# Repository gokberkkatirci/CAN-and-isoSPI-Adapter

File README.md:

# CAN and isoSPI Adapters

Two USB adapters for battery-management bench work. Both connect a host PC to isolated Classical CAN and isoSPI, with socketed controller modules and switchable CAN termination.

| | [Nano R4 · R0E](#nano-r4-adapter-r0e) | [Teensy 4.1 · T41-R0C](#teensy-41-adapter-t41-r0c) |
|---|:---:|:---:|
| Top view |  |  |
| Controller | Arduino Nano R4 (socketed) | Teensy 4.1 (socketed) |
| USB | Nano's own USB-C | Carrier USB-C for power and data |
| CAN ports | 1, screw terminal | 6, vertical DSUB-9 female (CiA 303-1 pinout) |
| CAN isolation | ISO1042 with isolated 5 V supply | Six independent ISO1042 channels, each with its own isolated 5 V supply |
| CAN termination | 120 Ω slide switch | 120 Ω slide switch on every port |
| isoSPI ports | 2 (MAIN, AUX) | 6 |
| Board | 82 × 64 mm, 4 layers | 216 × 120 mm, 6 layers |
| Prototype files | [Nano Gerbers, BOM and CPL](manufacturing/prototype/R0E/) | [Teensy Gerbers, BOM and CPL](manufacturing/prototype/T41-R0C/) |

> **Prototype status.** Both boards pass their recorded KiCad ERC, DRC and schematic-parity checks. Every JLCPCB part on both BOMs was in stock on 2026-11-24. Hardware bring-up and insulation qualification are pending. The 1,000 V DC pack and 3 m isoSPI cable targets remain unqualified. The manufacturing files are for prototype review. See the [bench verification plan](tests/verification-plan.md).

## Nano R4 adapter (R0E)

| Interface | Hardware |
|---|---|
| Controller | Arduino Nano R4 with headers (ABX00143), installed in J1/J2 |
| CAN | ISO1042DWR, up to 1 Mbit/s, isolated regulated supply, TVS and switchable 120 Ω |
| isoSPI | ADBMS6822 with MAIN and AUX on separate floating twisted pairs |
| isoSPI magnetics | Two CND-tek HM1238NLTP transformers, each specified for 1,000 V DC working voltage and basic insulation |

Orient the board with USB-C at the top. The left terminal is marked **CAN H**, **CAN L** and **GND** from top to bottom. This GND is the isolated CAN reference. Set the slide switch to **120R** when the adapter terminates an end of the bus. The two right terminals are **MAIN** and **AUX**, each a floating differential pair with **+** above **−**.

| Nano pins | Function |
|---|---|
| D4 / D5 | CAN TX / RX |
| D8 / A3 | CAN supply enable, active high / fault, active low |
| D13 / D11 / D12 | SPI clock / controller out / controller in |
| D10 / D9 | MAIN / AUX chip select |
| D2 / D3 | MAIN / AUX interrupt status |
| D6 / D7 | MAIN / AUX wake status |

R0E replaces three parts that JLCPCB no longer stocked: the isoSPI transformers (now HM1238NLTP), the CAN supply transformer (now MXPP6-3K6110) and the CAN LDO (now TPS7A1650-Q1). See the [R0E notes](docs/r0e.md). Mounting hole H3 is close to the AUX terminal and must take **nylon hardware only**; the silkscreen says so ([R0D notes](docs/r0d.md)).

- [KiCad project](hardware/kicad/CAN_isoSPI_adapter.kicad_pro), [schematic](hardware/kicad/CAN_isoSPI_adapter.kicad_sch) and [routed PCB](hardware/kicad/CAN_isoSPI_adapter.kicad_pcb)
- [Nano R4 firmware](firmware/README.md#nano-r4-adapter)
- [R0E fabrication files](manufacturing/prototype/R0E/README.md) and [checks](tests/R0E/)

## Teensy 4.1 adapter (T41-R0C)

Six isolated CAN ports on DSUB-9 connectors along one long edge and six isoSPI terminals along the opposite long edge. **Channel N** is one column: CAN N sits directly opposite isoSPI N, numbered 1–6 from left to right, and the same number is used on the silkscreen, in the schematic, in reference designators and in the firmware. Each adapter reports a unique ID and an optional stored label, so several can share one host. A single USB-C connector supplies power and USB data; the data lines reach the Teensy through two pogo pins that touch its USB device pads. **Keep the Teensy's VIN–VUSB pads joined** and never plug its own micro-USB.

> **Before powered bring-up:** Resolve the six direct ADBMS6822 INTR connections to the Teensy’s 3.3 V inputs.

R0C replaces the same three out-of-stock parts as the Nano R0E ([T41-R0C notes](docs/t41-r0c.md)). R0B fixed the USB path of R0A: the Teensy VUSB pin is powered again, the D+/D− lines lost their 90 mm test-pad stubs, and VBUS runs on a 1 mm outer-layer track ([T41-R0B notes](docs/t41-r0b.md)).

| Interface | Hardware |
|---|---|
| Controller | Teensy 4.1 with pins, in two 1 × 24 sockets |
| CAN1–CAN3 | Teensy FlexCAN1–3 (CAN3 is CAN FD capable) |
| CAN4–CAN6 | MCP2518FD controllers on SPI1, 40 MHz crystals |
| Each CAN port | ISO1042DWR, TPS2553 current-limited switch, SN6505B + MXPP6-3K6110 isolated supply, TPS7A1650-Q1 LDO, PESD2CANFD24V TVS, 120 Ω switch, power LED |
| CAN connector | DSUB-9 female: pin 2 CAN_L, pin 7 CAN_H, pins 3 and 6 CAN_GND, pin 5 and shell to a 1 MΩ ∥ 4.7 nF shield network |
| isoSPI | Three ADBMS6822, six HM1238NLTP transformers, six two-pole terminals |
| USB-C | 5.1 kΩ CC pull-downs read by the Teensy for power budgeting, USBLC6 ESD, 2 A PTC, SMAJ5.0A |

- [User manual](docs/user-manual-t41.md) — assembly, flashing, commands and usage examples
- [Hardware notes and pin map](hardware/teensy41/README.md)
- [KiCad project](hardware/teensy41/CAN6_isoSPI6_T41.kicad_pro), generated from [design.py](hardware/teensy41/tools/design.py)
- [Teensy firmware](firmware/README.md#teensy-41-adapter)
- [R0C fabrication files for JLCPCB](manufacturing/prototype/T41-R0C/README.md) and [checks](tests/T41-R0C/)

## Shared documentation

- [Design rationale](docs/hardware-plan.md), [decisions](docs/decisions.md), [component sourcing](docs/components.md) and [references](docs/references.md)
- [Bench verification plan](tests/verification-plan.md)
- [3D model sources](hardware/kicad/models/README.md) and [third-party materials](THIRD_PARTY.md)

## Prototype limits

The PCB rules require **8 mm copper clearance** around each floating isoSPI cable domain. The **1 kV DC** transformer working rating applies to the HM1238NLTP, which provides basic insulation. Protective insulation still needs to be established for the complete system, including PCB creepage, mounting, cables and enclosure. The CAN ports are intended for low-voltage CAN networks.

On 2026-11-24 JLCPCB stocked every part. The scarcest parts limit an order to about 23 Teensy boards or 139 Nano boards ([stock list](docs/components.md#stock-check-2026-11-24)). Recheck stock, placement rotations, through-hole assembly and socket fit before ordering. See the [design decisions](docs/decisions.md) and [manufacturing workflow](manufacturing/README.md).

No license has been selected yet; see [publication notes](docs/publication.md).

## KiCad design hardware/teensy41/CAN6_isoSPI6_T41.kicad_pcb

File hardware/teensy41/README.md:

# Teensy 4.1 adapter — six CAN, six isoSPI (R0C)

Open [CAN6_isoSPI6_T41.kicad_pro](CAN6_isoSPI6_T41.kicad_pro) in **KiCad 10.0.6**. The schematic, PCB placement, zones, design rules and manufacturing CSVs are generated from [tools/design.py](tools/design.py) by [tools/generate_t41.py](tools/generate_t41.py). Edit `design.py` and regenerate rather than editing the schematic and board separately. The R0B USB rework was applied to the routed R0A board with [tools/rework_r0b.py](tools/rework_r0b.py) ([T41-R0B notes](../../docs/t41-r0b.md)). The R0C part swap for JLCPCB stock was applied to the R0B board with [tools/rework_r0c.py](tools/rework_r0c.py) ([T41-R0C notes](../../docs/t41-r0c.md)).

## Board

- **216 × 120 mm**, six layers, 1.6 mm, six M3 holes, all passives 1206.
- **Bottom edge:** six vertical DSUB-9 female connectors (mating face up, 4-40 standoffs), CAN1 on the left. Each has its own 120 Ω slide switch (**120R** / **OFF**) and a green LED that lights when its isolated supply is on.
- **Top edge:** six isoSPI terminals, each directly opposite the CAN port with the same number; **+** is on the left of each pair.
- **Left edge:** USB-C for power and data. The Teensy plugs into J2/J3 with its USB end toward the USB-C connector.

| Layer | Use |
|---|---|
| F.Cu | Components, signals and ground fanouts |
| In1.Cu | Logic ground plane; a separate ground plane for each isolated CAN port |
| In2.Cu | Signals |
| In3.Cu | Signals and a +5 V pour |
| In4.Cu | Second logic ground plane and per-port isolated ground planes |
| B.Cu | Signals, logic ground pour and per-port isolated ground pours |

The isoSPI cable side of each transformer has no plane under it and keeps 8 mm of copper clearance to everything else. Each CAN port's isolated domain is kept 3 mm away from logic copper and from its neighbours. Both rules are in [CAN6_isoSPI6_T41.kicad_dru](CAN6_isoSPI6_T41.kicad_dru).

## Channel addressing

Channel **N** is one column of the board: DSUB-9 **CAN N** on the bottom edge and terminal **isoSPI N** directly above it on the top edge. Channels are numbered 1–6 from left to right, viewed from the component side with USB-C on the left. The same number is used on the silkscreen, in the schematic net names (`CANn_*`, `ISOn_*`), the reference designators (CAN parts are numbered n01–n12, so channel 4 uses U401, J401, SW401…) and the firmware commands.

| Channel | CAN controller | isoSPI bridge | Bridge channel |
|---|---|---|---|
| 1 | FlexCAN1 | U701 | 2 |
| 2 | FlexCAN2 | U701 | 1 |
| 3 | FlexCAN3 (CAN FD capable) | U801 | 2 |
| 4 | MCP2518FD U405 | U801 | 1 |
| 5 | MCP2518FD U505 | U901 | 2 |
| 6 | MCP2518FD U605 | U901 | 1 |

isoSPI transformers and terminals use T7xx/J7xx for channels 1–2, T8xx/J8xx for 3–4 and T9xx/J9xx for 5–6. Each adapter reports a factory-unique ID over USB, and a user label can be stored in EEPROM, so several adapters on one host can be addressed reliably. See the [firmware commands](../../firmware/README.md#usb-serial-commands-1).

## Test points

Thirteen 1.5 mm test pads are placed in two groups between the Teensy and the right mounting hole. Probe them with an oscilloscope or multimeter during bring-up.

| Label | Net | Group | Row |
|---|---|---|---|
| 5V | +5V | Left | 1 |
| GND | GND | Left | 1 |
| 3V3 | +3.3V | Left | 1 |
| FLT | CAN_PWR_FAULT | Left | 2 |
| D32 | Teensy pin 32 (spare) | Left | 2 |
| MOSI | ISO_MOSI (isoSPI SPI) | Right | 1 |
| MISO | ISO_MISO | Right | 1 |
| SCK | ISO_SCK | Right | 1 |
| TX1 | CAN1_TX (FlexCAN1) | Right | 1 |
| RX1 | CAN1_RX | Right | 1 |
| MOSI1 | MCP_MOSI (SPI1) | Right | 2 |
| MISO1 | MCP_MISO | Right | 2 |
| SCK1 | MCP_SCK | Right | 2 |

R0A also had VBUS, D+ and D− pads (TP4, TP7, TP8). R0B removed them because their long routes split the +5 V pour and put 90 mm stubs on the USB pair. The other pads keep their numbers.

## 3D view

Every fitted part has a model. Standard parts use the KiCad 10 library; the ADBMS6822, transformers, slide switch, pogo pins, USB-C receptacle and a mounted Teensy 4.1 use drawing-based VRML models from [../kicad/models](../kicad/models/README.md). Open **View → 3D Viewer** or run `kicad-cli pcb render --quality high`.

## Before first power-up

1. **Keep the VIN–VUSB pads joined** on the Teensy's underside (the factory state). The carrier feeds VIN from +5 V through D2 (Schottky), after F1 (2 A PTC), and the joined pads pass that supply on to VUSB, which powers the Teensy's USB PHY. R0A said to cut the pads; with them cut the Teensy will not enumerate.
2. Use the carrier USB-C only. J4 and J5 are pogo pins that press on the Teensy's USB device D−/D+ pads, so the Teensy enumerates and is programmed through the carrier connector. **Never plug the Teensy's micro-USB** while it is on the carrier: the carrier would drive 5 V back into that host port through VUSB.
3. Measure the D−/D+ pad positions on your Teensy against J4/J5 before assembly; see [open items](../../docs/decisions.md#teensy-41-adapter-decisions-r0a-2026-11-08). Check that the pogo pins stand upright after reflow, or fit them by hand as described in the [manufacturing notes](../../manufacturing/prototype/T41-R0C/README.md).

## CAN port wiring

| DSUB-9 pin | Signal |
|---|---|
| 2 | CAN_L |
| 7 | CAN_H |
| 3, 6 | Isolated CAN ground of that port |
| 5, shell | Shield, to that port's ground through 1 MΩ ∥ 4.7 nF 2 kV |
| 1, 4, 8, 9 | Not connected |

This is the CiA 303-1 layout used by PEAK PCAN adapters, so standard CAN cables and termination plugs fit.

## Teensy 4.1 pin map

| Teensy pin | Function | Teensy pin | Function |
|---|---|---|---|
| 22 / 23 | CAN1 TX / RX (FlexCAN1) | 17, 18, 19, 20, 21, 24 | CAN1–CAN6 supply enable, active high |
| 1 / 0 | CAN2 TX / RX (FlexCAN2) | 25 | CAN supply fault, wired-OR, active low |
| 31 / 30 | CAN3 TX / RX (FlexCAN3, FD capable) | 26 / 39 / 27 | SPI1 MOSI / MISO / SCK to MCP2518FD |
| 11 / 12 / 13 | SPI MOSI / MISO / SCK to ADBMS6822 | 38, 37, 36 | CAN4, CAN5, CAN6 MCP2518FD chip select |
| 10, 9, 8, 7, 6, 5 | isoSPI port 1–6 chip select | 35, 34, 33 | CAN4, CAN5, CAN6 MCP2518FD interrupt |
| 2, 3, 4, 14, 15, 16 | isoSPI port 1–6 INTR | 40 / 41 | USB-C CC1 / CC2 sense through 1 kΩ |
| 28 / 29 | Green OK LED / red fault LED | 32 | Spare, test pad TP6 (D32) |

Logic runs at 3.3 V from the Teensy's regulator. ADBMS6822 VDDS and MSTR use 3.3 V; VDD and VP use 5 V. ISO1042 VCC1 is 3.3 V and VCC2 is the port's isolated 5 V.

## Power

USB-C VBUS → 1 mm B.Cu track → F1 → SMAJ5.0A → +5 V plane; D2 feeds the Teensy VIN from +5 V. Each CAN port has a TPS2553 switch limited to about 200 mA (R_ILIM = 130 kΩ) feeding an SN6505B push-pull driver, a Maxinmicro MXPP6-3K6110 1:1.1 transformer, two B5819W rectifiers and a TPS7A1650-Q1 5 V LDO (100 mA; near dropout at full load, see [T41-R0C notes](../../docs/t41-r0c.md#still-open)). The switches stay off until firmware opens a port. Provisional worst case is about 110 mA from 5 V per transmitting CAN port plus about 250 mA for the Teensy, bridges and controllers, so all six ports need a 1.5 A or 3 A USB-C source. The firmware reads the source's CC advertisement and limits a default USB port to two open CAN ports.

## Regenerating

```sh
PY=/Applications/KiCad/KiCad.app/Contents/Frameworks/Python.framework/Versions/Current/bin/python3
export JAVA=/path/to/java FREEROUTING_JAR=/path/to/freerouting.jar
$PY hardware/teensy41/tools/generate_t41.py pcb      # schematic, project, rules, placement, ground and QFN fan-out
$PY hardware/teensy41/tools/generate_t41.py route    # Freerouting 2.x through a Specctra round trip
$PY hardware/teensy41/tools/generate_t41.py patch    # pours, zone fill, close leftovers, trim dangling copper
$PY hardware/teensy41/tools/generate_t41.py fab manufacturing/prototype/T41-R0C
```

How the generator gets a clean route:

- Every ground pad is fanned out to its plane before routing, and each ADBMS6822 pin gets a fixed escape to a via ring around the QFN, because an autorouter cannot reliably escape a 0.5 mm-pitch QFN with neighbouring decoupling.
- For routing, each ground pad and its fan-out get a private net, and the two ground-plane layers are removed from the Specctra file. The router therefore only uses F.Cu, In2, In3 and B.Cu, and leaves the planes intact.
- The isoSPI band and the CAN isolation gaps are temporary keepouts during routing; the final board checks them with the DRC rules instead.

Routing is not deterministic, so a regenerated board needs a new DRC run and a new manufacturing package. The `pcb` stage overwrites the routed board. The committed board reports zero ERC, DRC, unconnected-item and schematic-parity findings at all severities in KiCad 10.0.8 ([reports](../../tests/T41-R0C/)).

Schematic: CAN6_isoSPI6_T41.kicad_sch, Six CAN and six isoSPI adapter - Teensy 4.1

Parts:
C1, C4, C103, C105, C106, C203, C205, C206, C303, C305, C306, C403, C405, C406, C503, C505, C506, C603, C605, C606: 10uF; C_1206_3216Metric; MPN CL31A106KBHNNNE; JLCPCB Part # C13585
C2, C5, C102, C104, C107, C108, C109, C202, C204, C207, C208, C209, C302, C304, C307, C308, C309, C402, C404, C407, C408, C409, C412, C502, C504, C507, C508, C509, C512, C602, C604, C607, C608, C609, C612, C701, C702, C704, C706, C801, C802, C804, C806, C901, C902, C904, C906: 100nF; C_1206_3216Metric; MPN CL31B104KBCNNNC; JLCPCB Part # C24497
C3, C101, C201, C301, C401, C501, C601: 4.7nF 2kV; C_1206_3216Metric; MPN 1206B472K202NT; JLCPCB Part # C41017
C410, C411, C510, C511, C610, C611: 22pF; C_1206_3216Metric; MPN CC1206JKNPOCBN220; JLCPCB Part # C107174
C703, C705, C803, C805, C903, C905: 1uF; C_1206_3216Metric; MPN CL31B105KBHNNNE; JLCPCB Part # C1848
D1: SMAJ5.0A; D_SMA; MPN SMAJ5.0A; JLCPCB Part # C83329
D2, D101, D102, D201, D202, D301, D302, D401, D402, D501, D502, D601, D602: B5819W; D_SOD-123; MPN B5819W SL; JLCPCB Part # C8598
D3, D4, D104, D204, D304, D404, D504, D604: Green; LED_1206_3216Metric; MPN KT-1206G; JLCPCB Part # C14641
D5: Red; LED_1206_3216Metric; MPN KT-1206R; JLCPCB Part # C49018
D103, D203, D303, D403, D503, D603: PESD2CANFD24V-TR; SOT-23; MPN PESD2CANFD24V-TR; JLCPCB Part # C552486
F1: 2A PTC; Fuse_1206_3216Metric; MPN 1206L200PR; JLCPCB Part # C151163
H1, H2, H3, H4, H5, H6: M3 mounting hole; MountingHole_3.2mm_M3
J1: USB-C; USB_C_Receptacle_HRO_TYPE-C-31-M-12; MPN TYPE-C-31-M-12; JLCPCB Part # C165948
J2: Teensy 4.1 row GND-0-32; PinSocket_1x24_P2.54mm_Vertical; MPN HC-PM254-8.5H-1x24PZ; JLCPCB Part # C41376163
J3: Teensy 4.1 row VIN-23-33; PinSocket_1x24_P2.54mm_Vertical; MPN HC-PM254-8.5H-1x24PZ; JLCPCB Part # C41376163
J4: Pogo USB D-; Pogo_YTC1P-8535_D2.0mm; MPN YTC1P-8535-01; JLCPCB Part # C5221289
J5: Pogo USB D+; Pogo_YTC1P-8535_D2.0mm; MPN YTC1P-8535-01; JLCPCB Part # C5221289
J101: CAN1 DSUB-9F; DSUB-9_Socket_Vertical_P2.77x2.84mm_MountingHoles; MPN DS1034-09FBN044; JLCPCB Part # C19268322
J201: CAN2 DSUB-9F; DSUB-9_Socket_Vertical_P2.77x2.84mm_MountingHoles; MPN DS1034-09FBN044; JLCPCB Part # C19268322
J301: CAN3 DSUB-9F; DSUB-9_Socket_Vertical_P2.77x2.84mm_MountingHoles; MPN DS1034-09FBN044; JLCPCB Part # C19268322
J401: CAN4 DSUB-9F; DSUB-9_Socket_Vertical_P2.77x2.84mm_MountingHoles; MPN DS1034-09FBN044; JLCPCB Part # C19268322
J501: CAN5 DSUB-9F; DSUB-9_Socket_Vertical_P2.77x2.84mm_MountingHoles; MPN DS1034-09FBN044; JLCPCB Part # C19268322
J601: CAN6 DSUB-9F; DSUB-9_Socket_Vertical_P2.77x2.84mm_MountingHoles; MPN DS1034-09FBN044; JLCPCB Part # C19268322
J701: isoSPI 1; TerminalBlock_Phoenix_MKDS-1,5-2-5.08_1x02_P5.08mm_Horizont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; MPN 1715721; JLCPCB Part # C480516
J702: isoSPI 2; TerminalBlock_Phoenix_MKDS-1,5-2-5.08_1x02_P5.08mm_Horizont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; MPN 1715721; JLCPCB Part # C480516
J801: isoSPI 3; TerminalBlock_Phoenix_MKDS-1,5-2-5.08_1x02_P5.08mm_Horizont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; MPN 1715721; JLCPCB Part # C480516
J802: isoSPI 4; TerminalBlock_Phoenix_MKDS-1,5-2-5.08_1x02_P5.08mm_Horizont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; MPN 1715721; JLCPCB Part # C480516
J901: isoSPI 5; TerminalBlock_Phoenix_MKDS-1,5-2-5.08_1x02_P5.08mm_Horizont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; MPN 1715721; JLCPCB Part # C480516
J902: isoSPI 6; TerminalBlock_Phoenix_MKDS-1,5-2-5.08_1x02_P5.08mm_Horizont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; MPN 1715721; JLCPCB Part # C480516
R1, R2: 5.1k; R_1206_3216Metric; MPN 1206W4F5101T5E; JLCPCB Part # C26033
R3, R4, R7, R8: 1k; R_1206_3216Metric; MPN 1206W4F1001T5E; JLCPCB Part # C4410
R5, R103, R203, R303, R403, R503, R603: 1M; R_1206_3216Metric; MPN 1206W4F1004T5E; JLCPCB Part # C17927
R6, R107, R207, R307, R407, R507, R607: 2.2k; R_1206_3216Metric; MPN 1206W4F2201T5E; JLCPCB Part # C17948
R9, R106, R206, R306, R406, R408, R409, R506, R508, R509, R606, R608, R609, R701, R702, R801, R802, R901, R902: 10k; R_1206_3216Metric; MPN 1206W4F1002T5E; JLCPCB Part # C17902
R101, R102, R201, R202, R301, R302, R401, R402, R501, R502, R601, R602: 240R; R_1206_3216Metric; MPN 1206W4F2400T5E; JLCPCB Part # C17961
R104, R204, R304, R404, R504, R604: 130k; R_1206_3216Metric; MPN 1206W4F1303T5E; JLCPCB Part # C82092
R105, R205, R305, R405, R505, R605: 100k; R_1206_3216Metric; MPN 1206W4F1003T5E; JLCPCB Part # C17900
R703, R704, R803, R804, R903, R904: 100R; R_1206_3216Metric; MPN 1206W4F1000T5E; JLCPCB Part # C17901
SW101, SW201, SW301, SW401, SW501, SW601: 120R termination; EG1218; MPN EG1218; JLCPCB Part # C273394
T101, T201, T301, T401, T501, T601: MXPP6-3K6110; MPN MXPP6-3K6110; JLCPCB Part # C19943838
T701, T702, T801, T802, T901, T902: HM1238NLTP; MPN HM1238NLTP-CND; JLCPCB Part # C49230397
TP1, TP2, TP3, TP5, TP6, TP9, TP10, TP11, TP12, TP13, TP14, TP15, TP16: Test pad; TestPoint_Pad_D1.5mm
U1: USBLC6-2SC6; SOT-23-6; MPN USBLC6-2SC6; JLCPCB Part # C7519
U101, U201, U301, U401, U501, U601: ISO1042DWR; SOIC-16W_7.5x10.3mm_P1.27mm; MPN ISO1042DWR; JLCPCB Part # C1848126
U102, U202, U302, U402, U502, U602: TPS2553DBVR; SOT-23-6; MPN TPS2553DBVR; JLCPCB Part # C55266
U103, U203, U303, U403, U503, U603: SN6505BDBVR; SOT-23-6; MPN SN6505BDBVR; JLCPCB Part # C74518
U104, U204, U304, U404, U504, U604: TPS7A1650QDGNRQ1; MSOP-8-1EP_3x3mm_P0.65mm_EP1.73x1.85mm; MPN TPS7A1650QDGNRQ1; JLCPCB Part # C2832237
U405, U505, U605: MCP2518FDT-E/SL; SOIC-14_3.9x8.7mm_P1.27mm; MPN MCP2518FDT-E/SL; JLCPCB Part # C626758
U701, U801, U901: ADBMS6822WCCSZ-RL; ADBMS6822_05-08-7057; MPN ADBMS6822WCCSZ-RL; JLCPCB Part # C19190031
Y401, Y501, Y601: 40MHz; Crystal_SMD_3225-4Pin_3.2x2.5mm; MPN X322540MPB4SI; JLCPCB Part # C9010

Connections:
/+3V3: C4.1, C5.1, C109.1, C209.1, C309.1, C409.1, C412.1, C509.1, C512.1, C609.1, C612.1, C701.1, C702.1, C801.1, C802.1, C901.1, C902.1, J2.15 (3V3), J3.3 (3V3), R9.2, R106.2, R206.2, R306.2, R406.2, R408.2, R409.2, R506.2, R508.2, R509.2, R606.2, R608.2, R609.2, R701.2, R702.2, R801.2, R802.2, R901.2, R902.2, TP3.1, U101.1 (VCC1), U201.1 (VCC1), U301.1 (VCC1), U401.1 (VCC1), U405.14 (VDD), U501.1 (VCC1), U505.14 (VDD), U601.1 (VCC1), U605.14 (VDD), U701.1 (MSTR), U701.6 (VDDS), U701.25 (MSTR2), U701.30 (VDDS2), U801.1 (MSTR), U801.6 (VDDS), U801.25 (MSTR2), U801.30 (VDDS2), U901.1 (MSTR), U901.6 (VDDS), U901.25 (MSTR2), U901.30 (VDDS2)
/+5V: C1.1, C2.1, C102.1, C202.1, C302.1, C402.1, C502.1, C602.1, C703.1, C704.1, C705.1, C706.1, C803.1, C804.1, C805.1, C806.1, C903.1, C904.1, C905.1, C906.1, D1.1 (K), D2.2 (A), F1.2, R6.1, TP1.1, U102.1 (IN), U202.1 (IN), U302.1 (IN), U402.1 (IN), U502.1 (IN), U602.1 (IN), U701.12 (VDD), U701.13 (VP), U701.20 (VDD2), U701.21 (VP2), U801.12 (VDD), U801.13 (VP), U801.20 (VDD2), U801.21 (VP2), U901.12 (VDD), U901.13 (VP), U901.20 (VDD2), U901.21 (VP2)
/CAN1I_5V: C106.1, C107.1, C108.1, R107.1, U101.11 (VCC2), U101.16 (VCC2), U104.1 (OUT), U104.2 (NC)
/CAN1I_GND: C101.2, C105.2, C106.2, C107.2, C108.2, D103.3 (COMMON), D104.1 (K), J101.3 (CAN_GND), J101.6 (CAN_GND), R103.2, T101.5 (SEC_CT), U101.9 (GND2), U101.10 (GND2), U101.15 (GND2), U104.4 (GND), U104.6 (NC), U104.9 (EP)
/CAN1I_H: D103.1 (IO1), J101.7 (CAN_H), SW101.2 (COM), U101.13 (CANH)
/CAN1I_L: D103.2 (IO2), J101.2 (CAN_L), R101.2, R102.2, U101.12 (CANL)
/CAN1I_LED: D104.2 (A), R107.2
/CAN1I_RA: D101.2 (A), T101.6 (SEC1)
/CAN1I_RB: D102.2 (A), T101.4 (SEC2)
/CAN1I_RECT: C105.1, D101.1 (K), D102.1 (K), U104.5 (EN), U104.8 (IN)
/CAN1I_SHLD: C101.1, J101.5 (SHLD), J101.SH (SHELL), R103.1
/CAN1I_TERM: R101.1, R102.1, SW101.1 (ON)
/CAN1_EN: J3.10 (D17), R105.1, U102.3 (EN)
/CAN1_ILIM: R104.1, U102.5 (ILIM)
/CAN1_PPA: T101.3 (PRI2), U103.1 (D1)
/CAN1_PPB: T101.1 (PRI1), U103.3 (D2)
/CAN1_PWR: C103.1, C104.1, T101.2 (PRI_CT), U102.6 (OUT), U103.2 (VCC), U103.5 (EN)
/CAN1_RX: J3.4 (D23), TP13.1, U101.5 (RXD)
/CAN1_TX: J3.5 (D22), R106.1, TP12.1, U101.3 (TXD)
/CAN2I_5V: C206.1, C207.1, C208.1, R207.1, U201.11 (VCC2), U201.16 (VCC2), U204.1 (OUT), U204.2 (NC)
/CAN2I_GND: C201.2, C205.2, C206.2, C207.2, C208.2, D203.3 (COMMON), D204.1 (K), J201.3 (CAN_GND), J201.6 (CAN_GND), R203.2, T201.5 (SEC_CT), U201.9 (GND2), U201.10 (GND2), U201.15 (GND2), U204.4 (GND), U204.6 (NC), U204.9 (EP)
/CAN2I_H: D203.1 (IO1), J201.7 (CAN_H), SW201.2 (COM), U201.13 (CANH)
/CAN2I_L: D203.2 (IO2), J201.2 (CAN_L), R201.2, R202.2, U201.12 (CANL)
/CAN2I_LED: D204.2 (A), R207.2
/CAN2I_RA: D201.2 (A), T201.6 (SEC1)
/CAN2I_RB: D202.2 (A), T201.4 (SEC2)
/CAN2I_RECT: C205.1, D201.1 (K), D202.1 (K), U204.5 (EN), U204.8 (IN)
/CAN2I_SHLD: C201.1, J201.5 (SHLD), J201.SH (SHELL), R203.1
/CAN2I_TERM: R201.1, R202.1, SW201.1 (ON)
/CAN2_EN: J3.9 (D18), R205.1, U202.3 (EN)
/CAN2_ILIM: R204.1, U202.5 (ILIM)
/CAN2_PPA: T201.3 (PRI2), U203.1 (D1)
/CAN2_PPB: T201.1 (PRI1), U203.3 (D2)
/CAN2_PWR: C203.1, C204.1, T201.2 (PRI_CT), U202.6 (OUT), U203.2 (VCC), U203.5 (EN)
/CAN2_RX: J2.2 (D0), U201.5 (RXD)
/CAN2_TX: J2.3 (D1), R206.1, U201.3 (TXD)
/CAN3I_5V: C306.1, C307.1, C308.1, R307.1, U301.11 (VCC2), U301.16 (VCC2), U304.1 (OUT), U304.2 (NC)
/CAN3I_GND: C301.2, C305.2, C306.2, C307.2, C308.2, D303.3 (COMMON), D304.1 (K), J301.3 (CAN_GND), J301.6 (CAN_GND), R303.2, T301.5 (SEC_CT), U301.9 (GND2), U301.10 (GND2), U301.15 (GND2), U304.4 (GND), U304.6 (NC), U304.9 (EP)
/CAN3I_H: D303.1 (IO1), J301.7 (CAN_H), SW301.2 (COM), U301.13 (CANH)
/CAN3I_L: D303.2 (IO2), J301.2 (CAN_L), R301.2, R302.2, U301.12 (CANL)
/CAN3I_LED: D304.2 (A), R307.2
/CAN3I_RA: D301.2 (A), T301.6 (SEC1)
/CAN3I_RB: D302.2 (A), T301.4 (SEC2)
/CAN3I_RECT: C305.1, D301.1 (K), D302.1 (K), U304.5 (EN), U304.8 (IN)
/CAN3I_SHLD: C301.1, J301.5 (SHLD), J301.SH (SHELL), R303.1
/CAN3I_TERM: R301.1, R302.1, SW301.1 (ON)
/CAN3_EN: J3.8 (D19), R305.1, U302.3 (EN)
/CAN3_ILIM: R304.1, U302.5 (ILIM)
/CAN3_PPA: T301.3 (PRI2), U303.1 (D1)
/CAN3_PPB: T301.1 (PRI1), U303.3 (D2)
/CAN3_PWR: C303.1, C304.1, T301.2 (PRI_CT), U302.6 (OUT), U303.2 (VCC), U303.5 (EN)
/CAN3_RX: J2.22 (D30), U301.5 (RXD)
/CAN3_TX: J2.23 (D31), R306.1, U301.3 (TXD)
/CAN4I_5V: C406.1, C407.1, C408.1, R407.1, U401.11 (VCC2), U401.16 (VCC2), U404.1 (OUT), U404.2 (NC)
/CAN4I_GND: C401.2, C405.2, C406.2, C407.2, C408.2, D403.3 (COMMON), D404.1 (K), J401.3 (CAN_GND), J401.6 (CAN_GND), R403.2, T401.5 (SEC_CT), U401.9 (GND2), U401.10 (GND2), U401.15 (GND2), U404.4 (GND), U404.6 (NC), U404.9 (EP)
/CAN4I_H: D403.1 (IO1), J401.7 (CAN_H), SW401.2 (COM), U401.13 (CANH)
/CAN4I_L: D403.2 (IO2), J401.2 (CAN_L), R401.2, R402.2, U401.12 (CANL)
/CAN4I_LED: D404.2 (A), R407.2
/CAN4I_RA: D401.2 (A), T401.6 (SEC1)
/CAN4I_RB: D402.2 (A), T401.4 (SEC2)
/CAN4I_RECT: C405.1, D401.1 (K), D402.1 (K), U404.5 (EN), U404.8 (IN)
/CAN4I_SHLD: C401.1, J401.5 (SHLD), J401.SH (SHELL), R403.1
/CAN4I_TERM: R401.1, R402.1, SW401.1 (ON)
/CAN4_EN: J3.7 (D20), R405.1, U402.3 (EN)
/CAN4_ILIM: R404.1, U402.5 (ILIM)
/CAN4_PPA: T401.3 (PRI2), U403.1 (D1)
/CAN4_PPB: T401.1 (PRI1), U403.3 (D2)
/CAN4_PWR: C403.1, C404.1, T401.2 (PRI_CT), U402.6 (OUT), U403.2 (VCC), U403.5 (EN)
/CAN4_RX: U401.5 (RXD), U405.2 (RXCAN)
/CAN4_TX: R406.1, U401.3 (TXD), U405.1 (TXCAN)
/CAN4_XI: C410.1, U405.6 (OSC1), Y401.1 (X1)
/CAN4_XO: C411.1, U405.5 (OSC2), Y401.3 (X2)
/CAN5I_5V: C506.1, C507.1, C508.1, R507.1, U501.11 (VCC2), U501.16 (VCC2), U504.1 (OUT), U504.2 (NC)
/CAN5I_GND: C501.2, C505.2, C506.2, C507.2, C508.2, D503.3 (COMMON), D504.1 (K), J501.3 (CAN_GND), J501.6 (CAN_GND), R503.2, T501.5 (SEC_CT), U501.9 (GND2), U501.10 (GND2), U501.15 (GND2), U504.4 (GND), U504.6 (NC), U504.9 (EP)
/CAN5I_H: D503.1 (IO1), J501.7 (CAN_H), SW501.2 (COM), U501.13 (CANH)
/CAN5I_L: D503.2 (IO2), J501.2 (CAN_L), R501.2, R502.2, U501.12 (CANL)
/CAN5I_LED: D504.2 (A), R507.2
/CAN5I_RA: D501.2 (A), T501.6 (SEC1)
/CAN5I_RB: D502.2 (A), T501.4 (SEC2)
/CAN5I_RECT: C505.1, D501.1 (K), D502.1 (K), U504.5 (EN), U504.8 (IN)
/CAN5I_SHLD: C501.1, J501.5 (SHLD), J501.SH (SHELL), R503.1
/CAN5I_TERM: R501.1, R502.1, SW501.1 (ON)
/CAN5_EN: J3.6 (D21), R505.1, U502.3 (EN)
/CAN5_ILIM: R504.1, U502.5 (ILIM)
/CAN5_PPA: T501.3 (PRI2), U503.1 (D1)
/CAN5_PPB: T501.1 (PRI1), U503.3 (D2)
/CAN5_PWR: C503.1, C504.1, T501.2 (PRI_CT), U502.6 (OUT), U503.2 (VCC), U503.5 (EN)
/CAN5_RX: U501.5 (RXD), U505.2 (RXCAN)
/CAN5_TX: R506.1, U501.3 (TXD), U505.1 (TXCAN)
/CAN5_XI: C510.1, U505.6 (OSC1), Y501.1 (X1)
/CAN5_XO: C511.1, U505.5 (OSC2), Y501.3 (X2)
/CAN6I_5V: C606.1, C607.1, C608.1, R607.1, U601.11 (VCC2), U601.16 (VCC2), U604.1 (OUT), U604.2 (NC)
/CAN6I_GND: C601.2, C605.2, C606.2, C607.2, C608.2, D603.3 (COMMON), D604.1 (K), J601.3 (CAN_GND), J601.6 (CAN_GND), R603.2, T601.5 (SEC_CT), U601.9 (GND2), U601.10 (GND2), U601.15 (GND2), U604.4 (GND), U604.6 (NC), U604.9 (EP)
/CAN6I_H: D603.1 (IO1), J601.7 (CAN_H), SW601.2 (COM), U601.13 (CANH)
/CAN6I_L: D603.2 (IO2), J601.2 (CAN_L), R601.2, R602.2, U601.12 (CANL)
/CAN6I_LED: D604.2 (A), R607.2
/CAN6I_RA: D601.2 (A), T601.6 (SEC1)
/CAN6I_RB: D602.2 (A), T601.4 (SEC2)
/CAN6I_RECT: C605.1, D601.1 (K), D602.1 (K), U604.5 (EN), U604.8 (IN)
/CAN6I_SHLD: C601.1, J601.5 (SHLD), J601.SH (SHELL), R603.1
/CAN6I_TERM: R601.1, R602.1, SW601.1 (ON)
/CAN6_EN: J2.16 (D24), R605.1, U602.3 (EN)
/CAN6_ILIM: R604.1, U602.5 (ILIM)
/CAN6_PPA: T601.3 (PRI2), U603.1 (D1)
/CAN6_PPB: T601.1 (PRI1), U603.3 (D2)
/CAN6_PWR: C603.1, C604.1, T601.2 (PRI_CT), U602.6 (OUT), U603.2 (VCC), U603.5 (EN)
/CAN6_RX: U601.5 (RXD), U605.2 (RXCAN)
/CAN6_TX: R606.1, U601.3 (TXD), U605.1 (TXCAN)
/CAN6_XI: C610.1, U605.6 (OSC1), Y601.1 (X1)
/CAN6_XO: C611.1, U605.5 (OSC2), Y601.3 (X2)
/CAN_PWR_FAULT: J2.17 (D25), R9.1, TP5.1, U102.4 (FAULT), U202.4 (FAULT), U302.4 (FAULT), U402.4 (FAULT), U502.4 (FAULT), U602.4 (FAULT)
/CC1_SENSE: J3.17 (D40), R3.2
/CC2_SENSE: J3.16 (D41), R4.2
/GND: C1.2, C2.2, C3.2, C4.2, C5.2, C102.2, C103.2, C104.2, C109.2, C202.2, C203.2, C204.2, C209.2, C302.2, C303.2, C304.2, C309.2, C402.2, C403.2, C404.2, C409.2, C410.2, C411.2, C412.2, C502.2, C503.2, C504.2, C509.2, C510.2, C511.2, C512.2, C602.2, C603.2, C604.2, C609.2, C610.2, C611.2, C612.2, C701.2, C702.2, C703.2, C704.2, C705.2, C706.2, C801.2, C802.2, C803.2, C804.2, C805.2, C806.2, C901.2, C902.2, C903.2, C904.2, C905.2, C906.2, D1.2 (A), D3.1 (K), D4.1 (K), D5.1 (K), J1.A1 (GND), J1.A12 (GND), J1.B1 (GND), J1.B12 (GND), J2.1 (GND), J3.2 (GND), J3.15 (GND), R1.2, R2.2, R5.2, R104.2, R105.2, R204.2, R205.2, R304.2, R305.2, R404.2, R405.2, R504.2, R505.2, R604.2, R605.2, TP2.1, U1.2 (GND), U101.2 (GND1), U101.8 (GND1), U102.2 (GND), U103.4 (GND), U103.6 (CLK), U201.2 (GND1), U201.8 (GND1), U202.2 (GND), U203.4 (GND), U203.6 (CLK), U301.2 (GND1), U301.8 (GND1), U302.2 (GND), U303.4 (GND), U303.6 (CLK), U401.2 (GND1), U401.8 (GND1), U402.2 (GND), U403.4 (GND), U403.6 (CLK), U405.7 (VSS), U501.2 (GND1), U501.8 (GND1), U502.2 (GND), U503.4 (GND), U503.6 (CLK), U505.7 (VSS), U601.2 (GND1), U601.8 (GND1), U602.2 (GND), U603.4 (GND), U603.6 (CLK), U605.7 (VSS), U701.9 (GND), U701.14 (PHAPOL), U701.15 (RTO), U701.16 (XCVRMD), U701.17 (GND2), U701.22 (PHAPOL2), U701.23 (RTO2), U701.24 (XCVRMD2), U701.33 (EP), U801.9 (GND), U801.14 (PHAPOL), U801.15 (RTO), U801.16 (XCVRMD), U801.17 (GND2), U801.22 (PHAPOL2), U801.23 (RTO2), U801.24 (XCVRMD2), U801.33 (EP), U901.9 (GND), U901.14 (PHAPOL), U901.15 (RTO), U901.16 (XCVRMD), U901.17 (GND2), U901.22 (PHAPOL2), U901.23 (RTO2), U901.24 (XCVRMD2), U901.33 (EP), Y401.2 (GND), Y401.4 (GND), Y501.2 (GND), Y501.4 (GND), Y601.2 (GND), Y601.4 (GND)
/ISO1C_N: J701.1 (-), T701.4 (SEC-)
/ISO1C_P: J701.2 (+), T701.6 (SEC+)
/ISO1_IM: R703.2, T701.3 (PRI-), U701.18 (IM2)
/ISO1_IP: R703.1, T701.1 (PRI+), U701.19 (IP2)
/ISO2C_N: J702.1 (-), T702.4 (SEC-)
/ISO2C_P: J702.2 (+), T702.6 (SEC+)
/ISO2_IM: R704.2, T702.3 (PRI-), U701.10 (IM)
/ISO2_IP: R704.1, T702.1 (PRI+), U701.11 (IP)
/ISO3C_N: J801.1 (-), T801.4 (SEC-)
/ISO3C_P: J801.2 (+), T801.6 (SEC+)
/ISO3_IM: R803.2, T801.3 (PRI-), U801.18 (IM2)
/ISO3_IP: R803.1, T801.1 (PRI+), U801.19 (IP2)
/ISO4C_N: J802.1 (-), T802.4 (SEC-)
/ISO4C_P: J802.2 (+), T802.6 (SEC+)
/ISO4_IM: R804.2, T802.3 (PRI-), U801.10 (IM)
/ISO4_IP: R804.1, T802.1 (PRI+), U801.11 (IP)
/ISO5C_N: J901.1 (-), T901.4 (SEC-)
/ISO5C_P: J901.2 (+), T901.6 (SEC+)
/ISO5_IM: R903.2, T901.3 (PRI-), U901.18 (IM2)
/ISO5_IP: R903.1, T901.1 (PRI+), U901.19 (IP2)
/ISO6C_N: J902.1 (-), T902.4 (SEC-)
/ISO6C_P: J902.2 (+), T902.6 (SEC+)
/ISO6_IM: R904.2, T902.3 (PRI-), U901.10 (IM)
/ISO6_IP: R904.1, T902.1 (PRI+), U901.11 (IP)
/ISO_CS1: J2.12 (D10), R702.1, U701.29 (CS2)
/ISO_CS2: J2.11 (D9), R701.1, U701.5 (CS)
/ISO_CS3: J2.10 (D8), R802.1, U801.29 (CS2)
/ISO_CS4: J2.9 (D7), R801.1, U801.5 (CS)
/ISO_CS5: J2.8 (D6), R902.1, U901.29 (CS2)
/ISO_CS6: J2.7 (D5), R901.1, U901.5 (CS)
/ISO_INT1: J2.4 (D2), U701.31 (INTR2)
/ISO_INT2: J2.5 (D3), U701.7 (INTR)
/ISO_INT3: J2.6 (D4), U801.31 (INTR2)
/ISO_INT4: J3.13 (D14), U801.7 (INTR)
/ISO_INT5: J3.12 (D15), U901.31 (INTR2)
/ISO_INT6: J3.11 (D16), U901.7 (INTR)
/ISO_MISO: J2.14 (D12), TP10.1, U701.3 (POCI), U701.27 (POCI2), U801.3 (POCI), U801.27 (POCI2), U901.3 (POCI), U901.27 (POCI2)
/ISO_MOSI: J2.13 (D11), TP9.1, U701.2 (PICO), U701.26 (PICO2), U801.2 (PICO), U801.26 (PICO2), U901.2 (PICO), U901.26 (PICO2)
/ISO_SCK: J3.14 (D13), TP11.1, U701.4 (SCK), U701.28 (SCK2), U801.4 (SCK), U801.28 (SCK2), U901.4 (SCK), U901.28 (SCK2)
/LED_5V_A: D3.2 (A), R6.2
/LED_ERR: J2.21 (D29), R8.1
/LED_ERR_A: D5.2 (A), R8.2
/LED_OK: J2.20 (D28), R7.1
/LED_OK_A: D4.2 (A), R7.2
/MCP_CS4: J3.19 (D38), R408.1, U405.13 (nCS)
/MCP_CS5: J3.20 (D37), R508.1, U505.13 (nCS)
/MCP_CS6: J3.21 (D36), R608.1, U605.13 (nCS)
/MCP_INT4: J3.22 (D35), R409.1, U405.4 (nINT)
/MCP_INT5: J3.23 (D34), R509.1, U505.4 (nINT)
/MCP_INT6: J3.24 (D33), R609.1, U605.4 (nINT)
/MCP_MISO: J3.18 (D39), TP15.1, U405.12 (SDO), U505.12 (SDO), U605.12 (SDO)
/MCP_MOSI: J2.18 (D26), TP14.1, U405.11 (SDI), U505.11 (SDI), U605.11 (SDI)
/MCP_SCK: J2.19 (D27), TP16.1, U405.10 (SCK), U505.10 (SCK), U605.10 (SCK)
/T_SPARE32: J2.24 (D32), TP6.1
/T_VIN: D2.1 (K), J3.1 (VIN)
/USB_CC1: J1.A5 (CC1), R1.1, R3.1
/USB_CC2: J1.B5 (CC2), R2.1, R4.1
/USB_DM: J1.A7 (D-), J1.B7 (D-), J4.1, U1.3 (IO2), U1.4 (IO2)
/USB_DP: J1.A6 (D+), J1.B6 (D+), J5.1, U1.1 (IO1), U1.6 (IO1)
/USB_SHIELD: C3.1, J1.SH (SHIELD), R5.1
/VBUS: F1.1, J1.A4 (VBUS), J1.A9 (VBUS), J1.B4 (VBUS), J1.B9 (VBUS), U1.5 (VBUS)

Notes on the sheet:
Power and USB
Teensy 4.1
isoSPI 1-2
isoSPI 3-4
isoSPI 5-6
CAN1
CAN2
CAN3
CAN4
CAN5
CAN6
Teensy 4.1 sits in J2/J3 (8.5 mm sockets). Keep the VIN-VUSB pads joined: VUSB powers the USB PHY. Never plug the Teensy micro-USB.
J4/J5 pogo pins reach the Teensy USB device D-/D+ pads under the module; the carrier USB-C carries data and power.
CAN1-3 use Teensy FlexCAN1-3; CAN4-6 use MCP2518FD on SPI1. Each CAN port has its own isolated supply and ground.
DSUB-9 female, CiA 303-1 / PEAK pinout: 2 CAN_L, 7 CAN_H, 3 and 6 CAN_GND, 5 and shell to shield RC.
isoSPI ports use CND-tek HM1238NLTP (1000 V DC working, basic insulation). Keep 8 mm copper clearance per port.

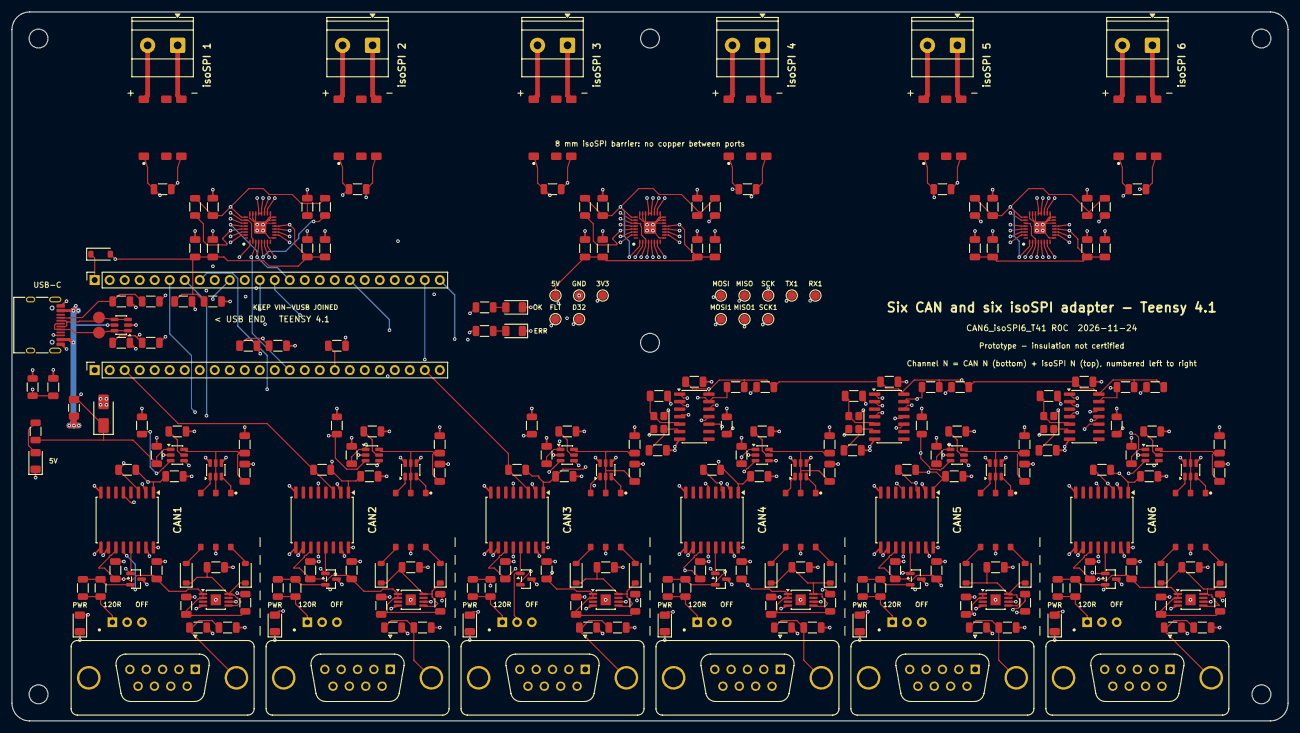
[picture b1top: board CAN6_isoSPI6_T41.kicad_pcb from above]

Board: 6 copper layers, 216.0 x 120.0 mm, 273 parts (0 on the bottom side), 175 nets.
